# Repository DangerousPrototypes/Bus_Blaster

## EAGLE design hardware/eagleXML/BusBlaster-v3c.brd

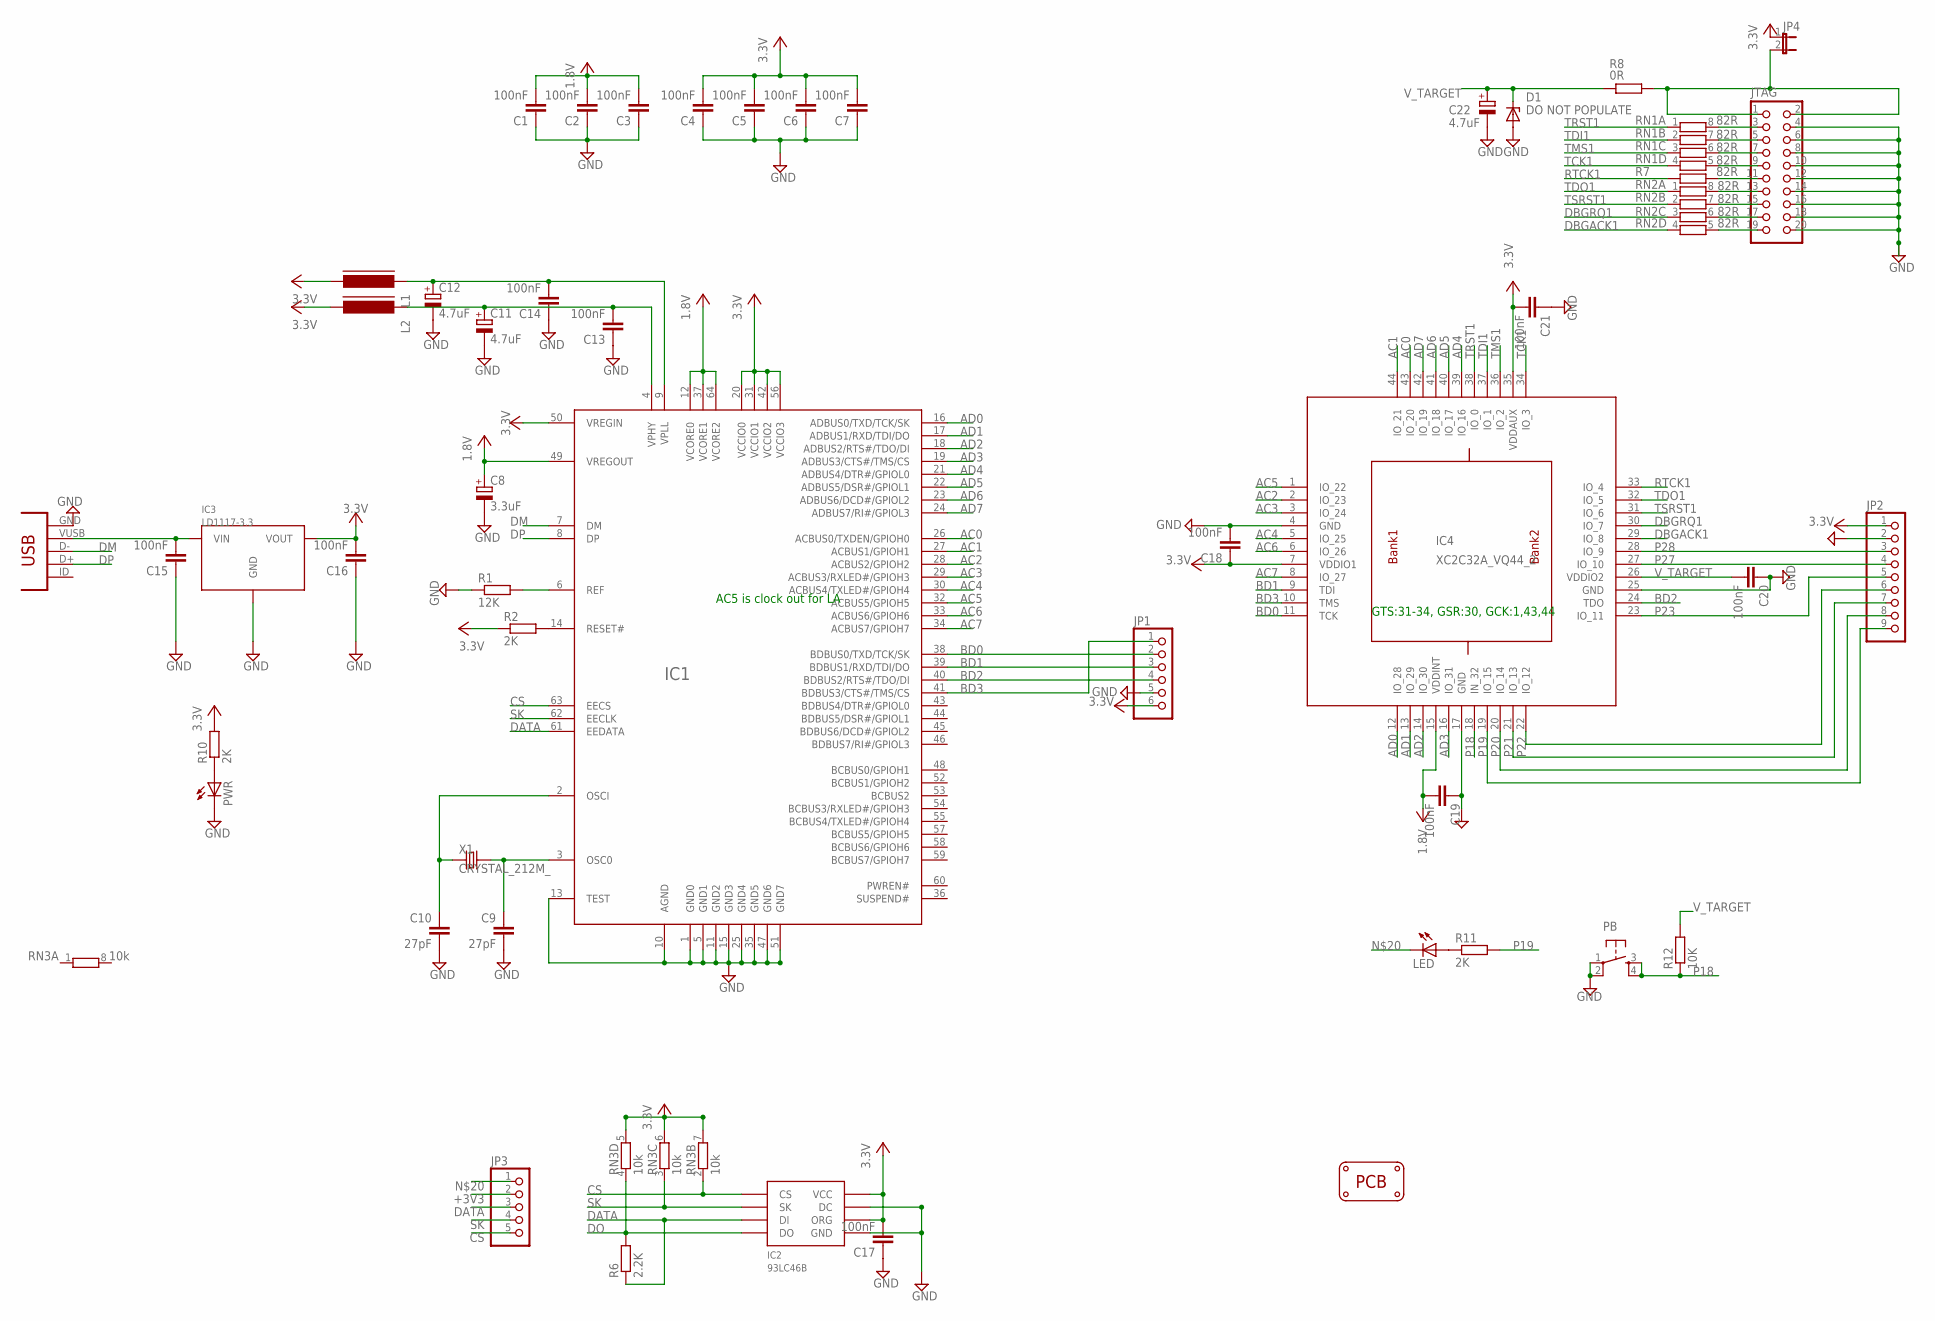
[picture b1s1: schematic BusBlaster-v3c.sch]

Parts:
C1, C2, C3, C4, C5, C6, C7, C13, C14, C15, C16, C17, C18, C19, C20, C21: 100nF; C603
C8: 3.3uF; SMC_A
C9, C10: 27pF; C603
C11, C12, C22: 4.7uF; SMC_A
D1: DO NOT POPULATE; SOD-123
IC1: FT2232H; LQFP64
IC2: 93LC46B; SOIC8
IC3: LD1117-3.3; SOT223
IC4: XC2C32A_VQ44_2; VQ44
JP1: PINHD-1X6; 1X06
JP2: PINHD-1X9; 1X09
JP3: PINHD-1X5; 1X05
JP4: JP1EJP; 1X02
JTAG: CON_HEADER_2X10-SHROUDED; PINSHRD_PTH_2X10
L1, L2: FERRITE_BEAD603; FB603
LED: LED805; LED-805
PB: SW-SMD-SMALL; TACT_SWITCH_SMALL
PCB3: PCB_DP_RECTANGLE-80X49; DP8049_V1
PWR: LEDCHIPLED_0805; CHIPLED_0805
R1: 12K; R603
R2, R10, R11: 2K; R603
R6: 2.2K; R603
R7: 82R; R603
R8: 0R; R1206
R12: 10K; R603
RN1, RN2: 82R; RN8P-4R-CRA06S
RN3: 10k; RN8P-4R-CRA06S
USB: CON-USB-MINI-BUSB1; CONN_USB_MINI-B
X1: CRYSTAL_212M_; 4X6

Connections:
1.8V: C1.2, C2.2, C3.2, C8.+, C19.2, IC1.12 (VCORE0), IC1.37 (VCORE1), IC1.49 (VREGOUT), IC1.64 (VCORE2), IC4.15 (VDDINT)
+3V3: C4.2, C5.2, C6.2, C7.2, C16.2, C17.2, C18.1, C21.2, IC1.20 (VCCIO0), IC1.31 (VCCIO1), IC1.42 (VCCIO2), IC1.50 (VREGIN), IC1.56 (VCCIO3), IC2.6 (ORG), IC2.8 (VCC), IC3.2 (VOUT), IC4.7 (VDDIO1), IC4.35 (VDDAUX), JP1.6, JP2.1, JP3.2, JP4.1, L1.2, L2.2, R2.1, R10.2, RN3.5 (2), RN3.6 (2), RN3.7 (2)
AC0: IC1.26 (ACBUS0/TXDEN/GPIOH0), IC4.43 (IO_20)
AC1: IC1.27 (ACBUS1/GPIOH1), IC4.44 (IO_21)
AC2: IC1.28 (ACBUS2/GPIOH2), IC4.2 (IO_23)
AC3: IC1.29 (ACBUS3/RXLED#/GPIOH3), IC4.3 (IO_24)
AC4: IC1.30 (ACBUS4/TXLED#/GPIOH4), IC4.5 (IO_25)
AC5: IC1.32 (ACBUS5/GPIOH5), IC4.1 (IO_22)
AC6: IC1.33 (ACBUS6/GPIOH6), IC4.6 (IO_26)
AC7: IC1.34 (ACBUS7/GPIOH7), IC4.8 (IO_27)
AD0: IC1.16 (ADBUS0/TXD/TCK/SK), IC4.12 (IO_28)
AD1: IC1.17 (ADBUS1/RXD/TDI/DO), IC4.13 (IO_29)
AD2: IC1.18 (ADBUS2/RTS#/TDO/DI), IC4.14 (IO_30)
AD3: IC1.19 (ADBUS3/CTS#/TMS/CS), IC4.16 (IO_31)
AD4: IC1.21 (ADBUS4/DTR#/GPIOL0), IC4.39 (IO_16)
AD5: IC1.22 (ADBUS5/DSR#/GPIOL1), IC4.40 (IO_17)
AD6: IC1.23 (ADBUS6/DCD#/GPIOL2), IC4.41 (IO_18)
AD7: IC1.24 (ADBUS7/RI#/GPIOL3), IC4.42 (IO_19)
BD0: IC1.38 (BDBUS0/TXD/TCK/SK), IC4.11 (TCK), JP1.2
BD1: IC1.39 (BDBUS1/RXD/TDI/DO), IC4.9 (TDI), JP1.3
BD2: IC1.40 (BDBUS2/RTS#/TDO/DI), IC4.24 (TDO), JP1.4
BD3: IC1.41 (BDBUS3/CTS#/TMS/CS), IC4.10 (TMS), JP1.1
CS: IC1.63 (EECS), IC2.1 (CS), JP3.5, RN3.2 (1)
DATA: IC1.61 (EEDATA), IC2.3 (DI), JP3.3, R6.1
DBGACK1: IC4.29 (IO_8), RN2.4 (1)
DBGRQ1: IC4.30 (IO_7), RN2.3 (1)
DM: IC1.7 (DM), USB.D-
DO: IC2.4 (DO), R6.2, RN3.4 (1)
DP: IC1.8 (DP), USB.D+
unnamed: C9.1, IC1.3 (OSC0), X1.2 (X2)
unnamed: C10.1, IC1.2 (OSCI), X1.1 (X1)
unnamed: IC1.14 (RESET#), R2.2
unnamed: IC1.6 (REF), R1.2
unnamed: C15.2, IC3.3 (VIN), USB.VUSB
unnamed: PWR.A, R10.1
unnamed: JTAG.3, RN1.8 (2)
unnamed: LED.A, R11.1
unnamed: JTAG.5, RN1.7 (2)
unnamed: JTAG.7, RN1.6 (2)
unnamed: JTAG.9, RN1.5 (2)
unnamed: JTAG.11, R7.2
unnamed: JTAG.13, RN2.8 (2)
unnamed: JTAG.15, RN2.7 (2)
unnamed: JTAG.17, RN2.6 (2)
unnamed: JTAG.19, RN2.5 (2)
unnamed: C1.1, C2.1, C3.1, C4.1, C5.1, C6.1, C7.1, C8.-, C9.2, C10.2, C11.-, C12.-, C13.1, C14.1, C15.1, C16.1, C17.1, C18.2, C19.1, C20.1, C21.1, C22.-, D1.A, IC1.1 (GND0), IC1.5 (GND1), IC1.10 (AGND), IC1.11 (GND2), IC1.13 (TEST), IC1.15 (GND3), IC1.25 (GND4), IC1.35 (GND5), IC1.47 (GND6), IC1.51 (GND7), IC2.5 (GND), IC2.7 (DC), IC3.1 (GND), IC4.4 (GND), IC4.17 (GND), IC4.25 (GND), JP1.5, JP2.2, JP3.1, JTAG.4, JTAG.6, JTAG.8, JTAG.10, JTAG.12, JTAG.14, JTAG.16, JTAG.18, JTAG.20, LED.C, PB.1, PB.2, PWR.C, R1.1, USB.GND
P18: IC4.18 (IN_32), PB.3, PB.4, R12.1
P19: IC4.19 (IO_15), JP2.9, R11.2
P20: IC4.20 (IO_14), JP2.8
P21: IC4.21 (IO_13), JP2.7
P22: IC4.22 (IO_12), JP2.6
P23: IC4.23 (IO_11), JP2.5
P27: IC4.27 (IO_10), JP2.4
P28: IC4.28 (IO_9), JP2.3
RTCK1: IC4.33 (IO_4), R7.1
SK: IC1.62 (EECLK), IC2.2 (SK), JP3.4, RN3.3 (1)
TCK1: IC4.34 (IO_3), RN1.4 (1)
TDI1: IC4.37 (IO_1), RN1.2 (1)
TDO1: IC4.32 (IO_5), RN2.1
TMS1: IC4.36 (IO_2), RN1.3 (1)
TRST1: IC4.38 (IO_0), RN1.1
TSRST1: IC4.31 (IO_6), RN2.2 (1)
VPHY: C11.+, C13.2, IC1.4 (VPHY), L2.1
VPLL: C12.+, C14.2, IC1.9 (VPLL), L1.1
V_TARGET: C20.2, C22.+, D1.C, IC4.26 (VDDIO2), R8.1, R12.2
V_TARGET_UNREG: JP4.2, JTAG.1, JTAG.2, R8.2

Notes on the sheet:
GTS:31-34, GSR:30, GCK:1,43,44
AC5 is clock out for LA

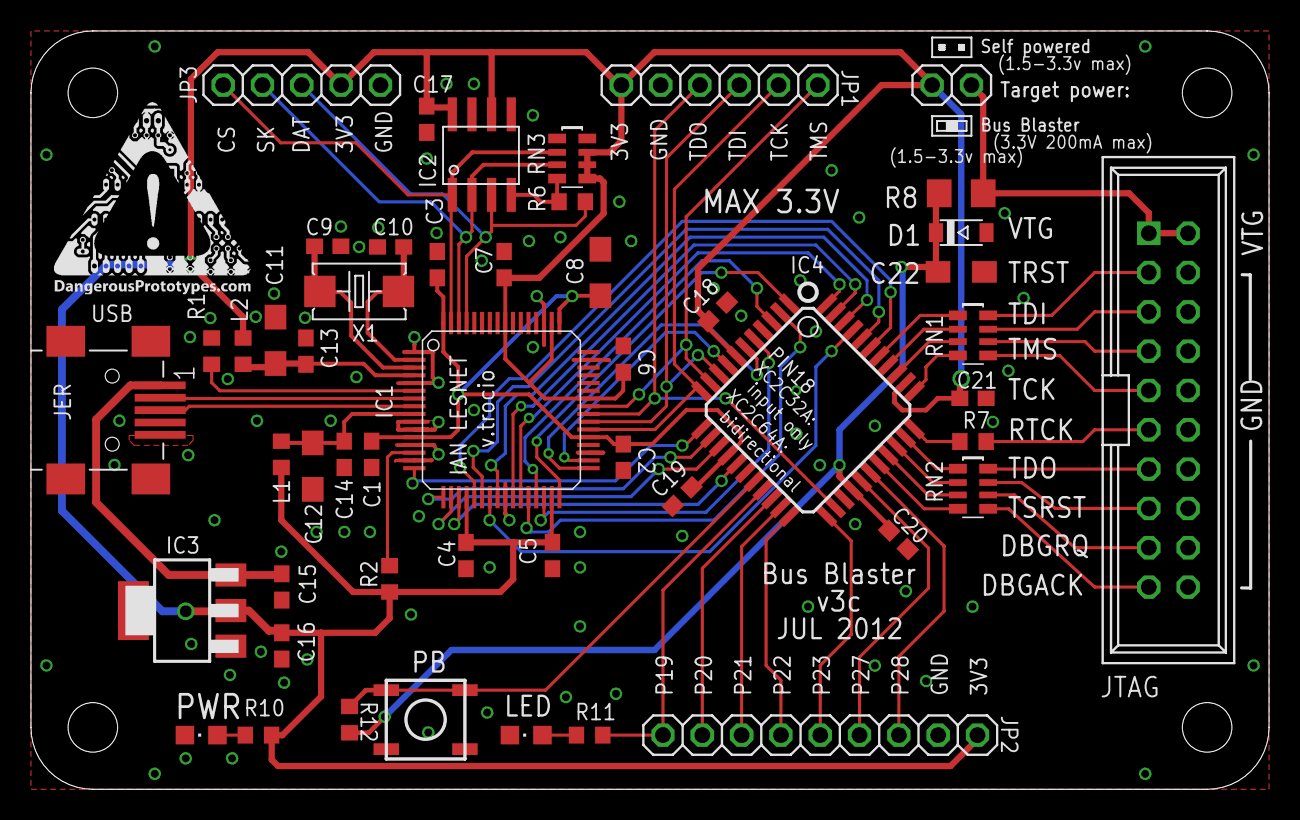
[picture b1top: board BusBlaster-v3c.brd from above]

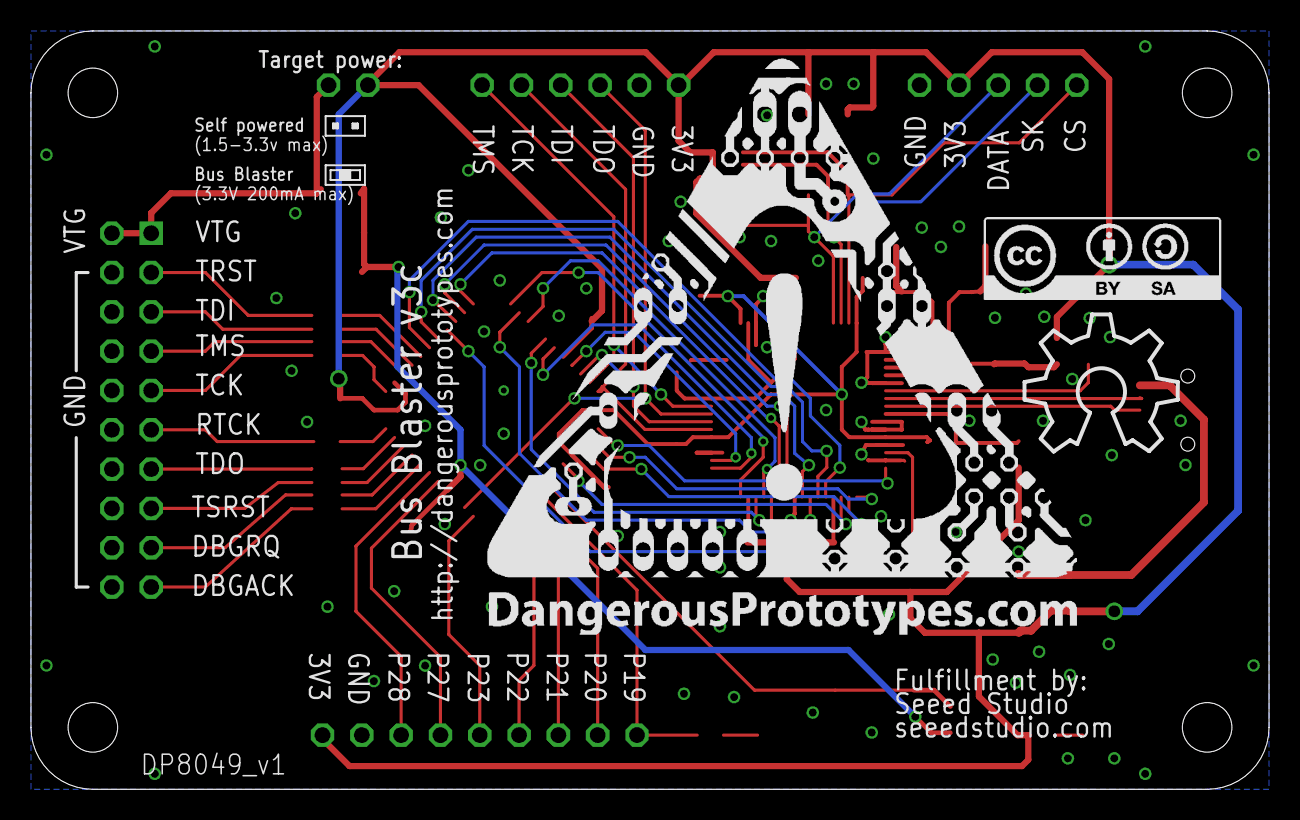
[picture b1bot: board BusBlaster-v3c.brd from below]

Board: 2 copper layers, 80.0 x 49.0 mm, 59 parts (5 on the bottom side), 66 nets.

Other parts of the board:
U$1: DP_LOGO_ART_1.5X1.5
U$2: DP_LOGO_ART_0.5X0.5
U$3: CC-BY-SA
U$5: OSHW_10X350_NOTEXT
U$6, U$9: adasdsd; JUMP2_DESC_ON
U$7, U$8: JUMP2_DESC_OFF

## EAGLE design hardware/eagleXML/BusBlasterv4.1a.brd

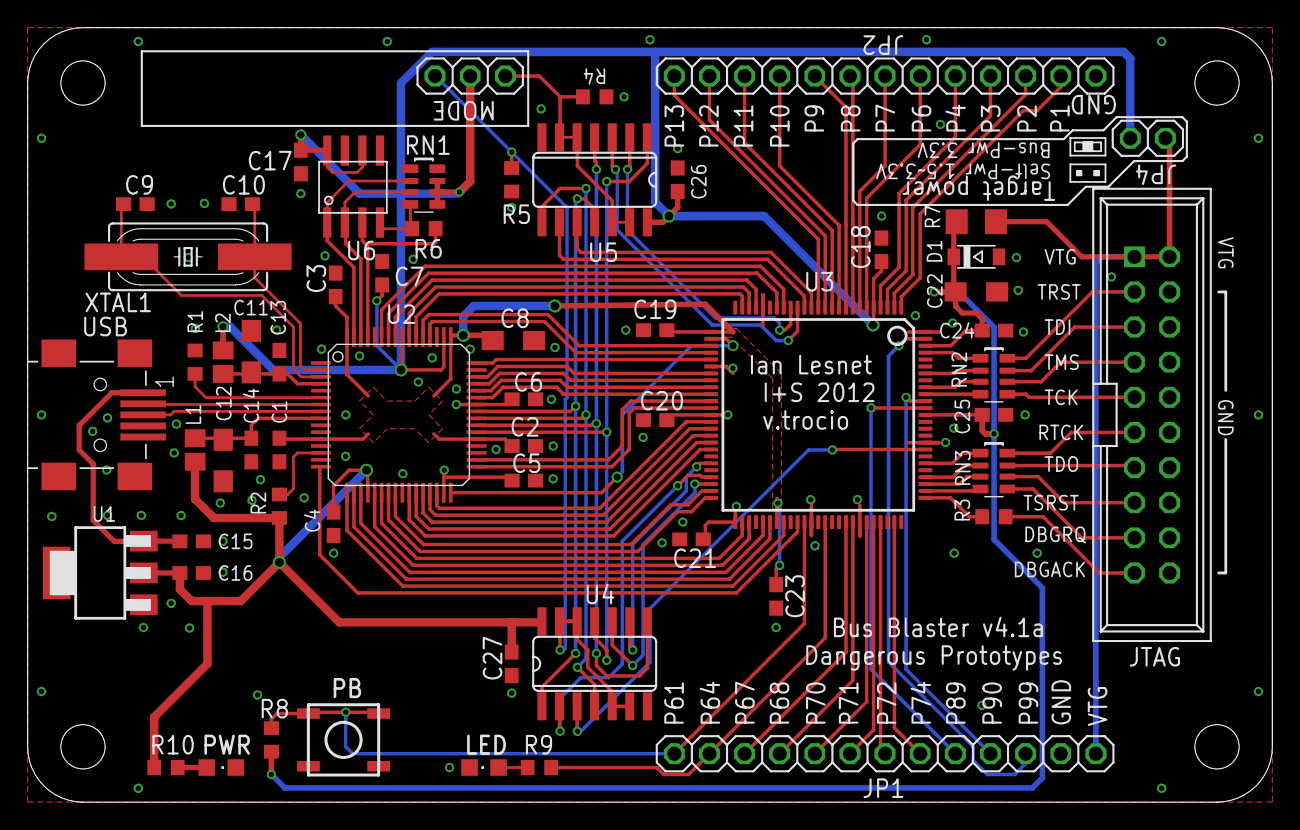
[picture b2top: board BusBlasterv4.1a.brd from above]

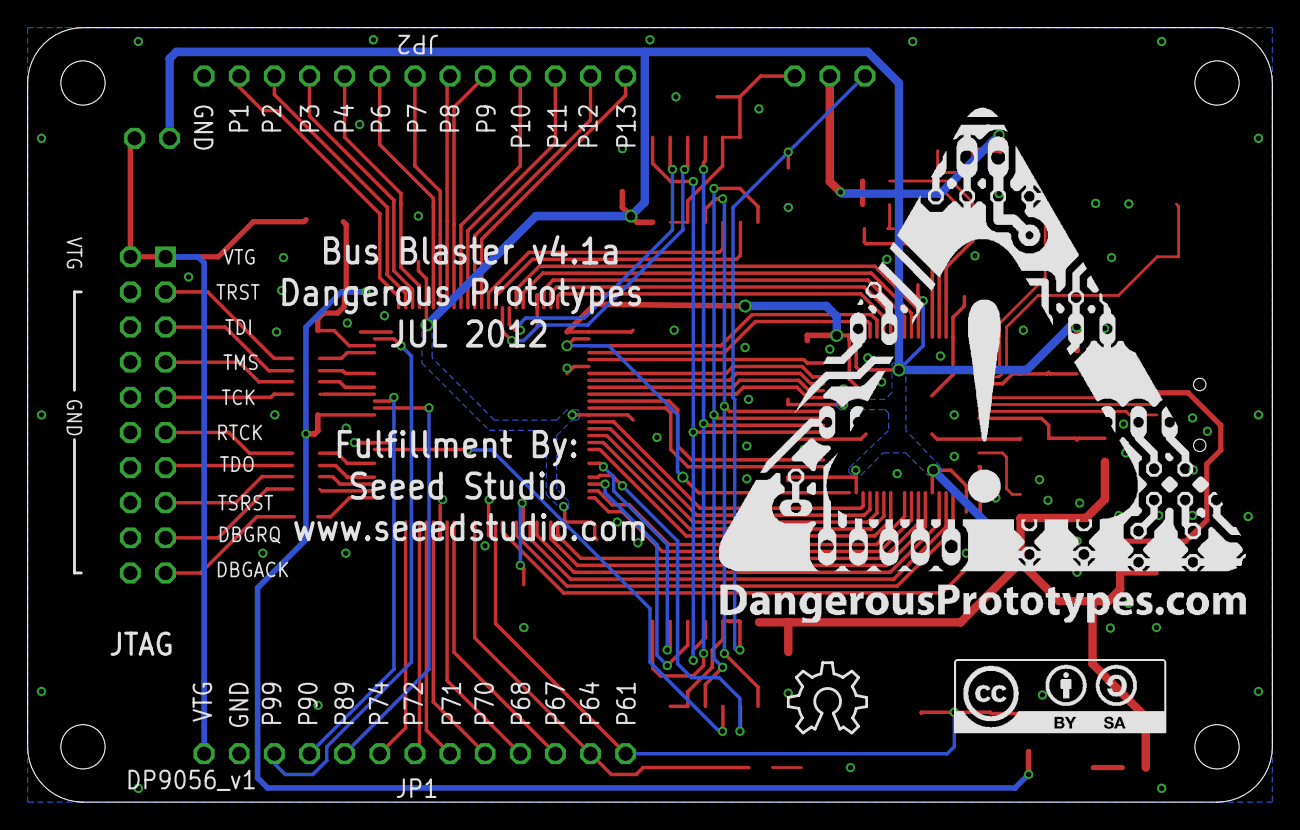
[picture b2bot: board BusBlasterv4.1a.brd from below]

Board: 2 copper layers, 90.0 x 56.0 mm, 65 parts (3 on the bottom side), 103 nets.

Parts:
C1, C2, C3, C4, C5, C6, C7, C13, C14, C15, C16, C17, C18, C19, C20, C21, C23, C24, C25, C26, C27: 100nF; C603
C8: 3.3uF; SMC_A
C9, C10: 27pF; C603
C11, C12, C22: 4.7uF; SMC_A
D1: DO NOT POPULATE; SOD-123
JP1, JP2: 1X13
JP4: 1X02
JTAG: CON_HEADER_2X10-SHROUDED; PINSHRD_PTH_2X10
L1, L2: FB603
LED: LED-805
MODE: 1X03
PB: TACT_SWITCH_SMALL
PCB1: PCB_DP_RECTANGLE-56X90; DP9056_V1
PWR: CHIPLED_0805
R1: 12K; R603
R2, R9: 1K; R603
R3: 82R; R603
R4, R5, R8: 10K; R603
R6: 2.2K; R603
R7: 0R; R1206
R10: 470; R603
RN1: 10k; RN8P-4R-CRA06S
RN2, RN3: 82R; RN8P-4R-CRA06S
U1: SOT223
U2: LQFP64@1
U3: XC2C64A; VQ100
U4, U5: 4066D; SO14
U6: 93LC46B; SOIC8
U$1: DP_LOGO1.5X1.5; DP_LOGO_ART_1.5X1.5
U$2: CC-BY-SA
U$3: OSHW_8X200_NOTEXT
U$4: LABEL_JUMPER_1X3; JUMP3_DESC
U$7: LABEL_JUMPER_1X2; JUMP2_DESC
USB: CON-USB-MINI-BUSB1; CONN_USB_MINI-B
XTAL1: HC-49U

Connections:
1: JP2.2, U3.1
1.8V: C1.2, C2.2, C3.2, C8.+, C19.2, C23.2, U2.12, U2.37, U2.49, U2.64, U3.26, U3.57
2: JP2.3, U3.2
3: JP2.4, U3.3
4: JP2.5, U3.4
6: JP2.6, U3.6
7: JP2.7, U3.7
8: JP2.8, U3.8
9: JP2.9, U3.9
10: JP2.10, U3.10
11: JP2.11, U3.11
12: JP2.12, U3.12
13: JP2.13, U3.13
61: JP1.13, PB.3, PB.4, R8.1, U3.61
64: JP1.12, R9.2, U3.64
67: JP1.11, U3.67
68: JP1.10, U3.68
70: JP1.9, U3.70
71: JP1.8, U3.71
72: JP1.7, U3.72
74: JP1.6, U3.74
89: JP1.5, U3.89
90: JP1.4, U3.90
99: JP1.3, U3.99
+3V3: C4.2, C5.2, C6.2, C7.2, C16.2, C17.2, C18.2, C20.2, C21.2, C26.2, C27.2, JP4.1, L1.2, L2.2, MODE.2, R2.1, R10.2, RN1.5, RN1.6, RN1.7, U1.2, U2.20, U2.31, U2.42, U2.50, U2.56, U3.5, U3.38, U3.51, U4.14, U5.14, U6.6, U6.8
AC0: U2.26, U3.43
AC1: U2.27, U3.42
AC2: U2.28, U3.41
AC3: U2.29, U3.40
AC4: U2.30, U3.39
AC5: U2.32, U3.27
AC6: U2.33, U3.37
AC7: U2.34, U3.36
AD0: U2.16, U3.60
AD1: U2.17, U3.58
AD2: U2.18, U3.56
AD3: U2.19, U3.55
AD4: U2.21, U3.53
AD5: U2.22, U3.52
AD6: U2.23, U3.50
AD7: U2.24, U3.49
BC0: U2.48, U3.30
BC1: U2.52, U3.29
BC2: U2.53, U3.28
BC3: U2.54, U3.24
BC4: U2.55, U3.23
BC5: U2.57, U3.22
BC6: U2.58, U3.19
BC7: U2.59, U3.18
BD0: U2.38, U4.11, U5.1
BD0_: U3.17, U5.2
BD1: U2.39, U4.8, U5.4
BD1_: U3.16, U5.3
BD2: U2.40, U4.4, U5.8
BD2_: U3.15, U5.9
BD3: U2.41, U4.1, U5.11
BD3_: U3.14, U5.10
BD4: U2.43, U3.35
BD5: U2.44, U3.34
BD6: U2.45, U3.33
BD7: U2.46, U3.32
CS: RN1.2, U2.63, U6.1
DATA: R6.1, U2.61, U6.3
DBGACK1: R3.1, U3.76
DBGRQ1: RN3.4, U3.77
DM: U2.7, USB.D-
DO: R6.2, RN1.4, U6.4
DP: U2.8, USB.D+
GND: C1.1, C2.1, C3.1, C4.1, C5.1, C6.1, C7.1, C8.-, C9.2, C10.2, C11.-, C12.-, C13.1, C14.1, C15.1, C16.1, C17.1, C18.1, C19.1, C20.1, C21.1, C22.-, C23.1, C24.1, C25.2, C26.1, C27.1, D1.A, JP1.2, JP2.1, JTAG.4, JTAG.6, JTAG.8, JTAG.10, JTAG.12, JTAG.14, JTAG.16, JTAG.18, JTAG.20, LED.C, PB.1, PB.2, PWR.C, R1.1, R4.1, R5.2, U1.1, U2.1, U2.5, U2.10, U2.11, U2.13, U2.15, U2.25, U2.35, U2.47, U2.51, U3.21, U3.31, U3.62, U3.69, U3.84, U3.100, U4.7, U5.7, U6.5, U6.7, USB.GND
unnamed: C9.1, U2.3, XTAL1.2
unnamed: C10.1, U2.2, XTAL1.1
unnamed: R2.2, U2.14
unnamed: R1.2, U2.6
unnamed: C15.2, U1.3, USB.VUSB
unnamed: PWR.A, R10.1
unnamed: LED.A, R9.1
unnamed: JTAG.3, RN2.8
unnamed: JTAG.5, RN2.7
unnamed: JTAG.7, RN2.6
unnamed: JTAG.9, RN2.5
unnamed: JTAG.11, RN3.8
unnamed: JTAG.13, RN3.7
unnamed: JTAG.15, RN3.6
unnamed: JTAG.17, RN3.5
unnamed: JTAG.19, R3.2
unnamed: MODE.3, R5.1, U4.5, U4.6, U4.12, U4.13
unnamed: MODE.1, R4.2, U5.5, U5.6, U5.12, U5.13
RTCK1: RN3.1, U3.81
SK: RN1.3, U2.62, U6.2
TCK: U3.48, U4.10
TCK1: RN2.4, U3.91
TDI: U3.45, U4.9
TDI1: RN2.2, U3.94
TDO: U3.83, U4.3
TDO1: RN3.2, U3.79
TMS: U3.47, U4.2
TMS1: RN2.3, U3.92
TRST1: RN2.1, U3.97
TSRST1: RN3.3, U3.78
VPHY: C11.+, C13.2, L2.1, U2.4
VPLL: C12.+, C14.2, L1.1, U2.9
VT: C22.+, C24.2, C25.1, D1.C, R7.1, R8.2, U3.88, U3.98
VTG: JP1.1, JP4.2, JTAG.1, JTAG.2, R7.2

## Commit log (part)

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2012-07-23 updated v3 and v4 shrouded header with the correct silk, fix v4 "Fufillment" mispelling. Please use latest v3c and v4.1a
2012-07-23 Bus Blaster v3c 3d model and rendering
2012-07-24 Added parts: KSZ8851SNL, TPS6120X, 2X08 HEADER, 3x6 mm 2pins switch, 1.8" TFT LCD Added 2x10 Shrouded Pin Header variant to existing 2x10 Header
2012-07-25 Bus Blaster v3 svg files, and BoM
2012-07-25 Exploaded sob case assemplby 3d model
2012-08-03 Parts Added: 3.3v, 5v, vusb, gnd supply symbols, 2 and 3 pins wire to board screw terminal block, USB AF SMD. Parts updated: 2 and 3 pins jumper description change layer to tDocu.
2012-08-08 Added 74AC573 in SOIC-20 changed Oscillator prefix to 'X'
2012-08-09 Added: FT311D in LQFP-32
2012-08-14 Changes to USB interrupt from JTR
2012-08-14 small fix to BPv4 bootloader (comment in wrong place)
    http://dangerousprototypes.com/forum/viewtopic.php?f=28&t=3441&start=45#p42466
2012-08-14 UART inverse transmit pin was omitted in all BP versions:
    http://dangerousprototypes.com/track/view.php?id=47
2012-08-16 Bus Pirate Demo board firmware
2012-08-20 Added device: 23LC1024 SRAM in SOIC-8
2012-08-27 update to blog theme with header fix, switch for contest theme.
2012-08-27 blog theme contest template update
2012-09-04 Added devices: 74HC595 and 74141 Added footprint: DIL16 Updated: removed extra mounting holes on DP6060 Added schematic symbol: 12V, -12V and -5V Added Logo: Flame logo
2012-09-04 revised credit card sized PCB based on ISO.IEC 7810 ID-1 identification cards sizes, size changed from 85 x 56 mm to 85.60 x 53.98 mm
2012-09-04 update Standard rectangular PCBs devices
2012-09-06 little file reshuffeling in the ATX laser cutt files
2012-09-06 1.8 TFT design files
2012-09-07 Added: IN-12 Nixie tube display, IN-12 Socket cutout footprint Fixed: IN-12 Socket
2012-09-10 Sick of beige generic model, and render images
2012-09-12 first commit of DP KiCAD part library
2012-09-12 DP KiCAD parts
2012-09-13 .lib and .mod files converted using eagle2kicad-0.d.ulp from http://www.modulbot.com/download.html Fixed undefined DRAW command when loading to symbol library to KiCAD
2012-09-19 Added: INA138 device
2012-09-20 Bus Pirate v4 Sick of Beige case laser cutting files and partlist(BOM)
2012-09-24 maker faire new york banner
2012-09-24 Done the changes related to global->instance variables suggested by Jim, corrected some variable name typos and got rid of console debug messages.
2012-09-24 Added new Logic shrimp v2b, this version uses 23LC1024 SRAM
2012-09-25 initial Smoke Tester project folder
2012-09-25 Board files
2012-09-26 swapped drain and source pin of the p-mosfet controlling fuse blown switch
2012-09-27 OHS 2012 presentations
2012-10-01 Smoke Tester 3D model and renders
2012-10-07 Adding a vertical ATX socket from the Molex MiniFit Jr. line.
    Discrete sockets (key'ed and rectangular) are provided in separate files so they can be easily added to create different configurations. Each socket is made to be "stackable" on both sides, so you'll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
2012-10-07 adding an assortment of 3d models. They should all have origins centered properly about the pins. These were not checked thoroughly, but do appear to be generally correct. Most models are tweaked fro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
    The QFN32 is original and should be extremely easy to scale and accommodate other numbers of pins.
2012-10-08 Added: D8035E VFD board, composed of 3 boards. Board A, B and C
2012-10-08 Added: PTH variant of 2.1mm DC Barrel Connector with milled hole pads
2012-10-08 VFD Board, render and 3D model..
2012-10-10 first cut at molex KK series connectors. The 1x2 should be modeled in such a way that it's side stackable, so it will be easy to make additional even numbered connectors. These were based on a model 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
    These should be "close enough" for most purposes, alignment appears to be off a bit on the 4pos header though.
2012-10-10 ATO fuse clip, ATO fuse holder, and ATO jumper. Created from a minimal datasheet from Littlefuse 01000057Z.
    Can be found at Mouser:
    http://www.mouser.com/ProductDetail/Littelfuse/01000057Z/?qs=sGAEpiMZZMtN62bhLohzxVzkiLrmT5C%2f
    Other alternatives for high current voltage selection were discussed here:
    http://dangerousprototypes.com/forum/viewtopic.php?f=56&t=4509
2012-10-10 Added: 3D models for 2 trough-hole IC and a metalized Capacitor.
2012-10-10 Added SF303GJ26-3 JOYSTICK
2012-10-16 rearanged SID SVN, and aded the mauf resources and sales page foleder...as wlell as the sales page txt
2012-10-18 adding some 3.5mm side stacking screw terminals. The model is based on a phoenix 1984617, but should be representative of most side-stacking 3.5mm screw terminals.
    An individual component is also included, which should makes it really easy to quickly generate any number of positions (just do a move/copy, explode the components, and erase the lines along the sea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
2012-10-18 correcting the naming for the 2512 resistor model
2012-10-18 Added device: MicrosSD fold type socket, PIC24F16KA102, 1x2 SMD solder jumper. fix Arduino 1x8 header containing pin 8 - 13, offset ed location.
2012-10-18 Bus Blaster v4 test buffer project
2012-10-19 fix PIC24F16KA102 vector text overlap on its symbol Add SOIC-14 package on PIC16F1823
2012-10-22 Soldering Iron Driver renderings and 3D model
2012-10-25 Added projects: DP6037 protoboard v1, DP6037_PTH v1 and DP6037_SMD v1
2012-10-25 add project: FT230x_LTC4053_BB_proto_area.v1a
2012-10-25 Add project: FT311 breakout board v1b
2012-10-30 added: 1x08 and 1x06 0.1 pitch SMD female header
2012-10-30 added DIL-28 PTH to SMD socket
2012-10-31 Added manufacturing files for updated ATX board acrylic case
2012-11-05 added: 4.5 x 4.5 SMD Trimmer, model 3314G
2012-11-07 added right angled 0.1inch 1x06 male header. expanded M1X4, M1X6, M1X8 pads to 1.632mm and drill size to 1.02mm
2012-11-13 added a 1x06 right angled header and a 2x03 SMD straight male headers.
2012-11-15 initial xQFP protoboards folder
2012-11-15 add 0.50mm, 0.65mm and 0.80mm xQFP V1 protoboards
2012-11-22 added ICSP with pogo pin as connector
2012-11-22 added v2.1, LCD_Backpack_1.8_TFT with pogo footprint ICSP
2012-11-30 added 0.50, 0.65 and 0.80 mm pitch universal QFP footprint and QFP breakout board These footprint are licensed: CC-BY-SA
2012-12-05 commit PIC TQFP-100 breakout v1 and v2
2012-12-06 added protoboard with 0.65mm and 0.80mm xQFP
2012-12-07 added BP v4e, fix odd angled placement, no 45 degrees placement anymore. replaced ICSP header with miniature ICSP footprint
2012-12-07 updated 0.5, 0.65 and 0.8 xQFP protoboards by adding a USB footprint. 2-3 SOT-23-6 footprints were removed to fit the usb
2012-12-10 added a 6 way SOLO stacker connector and footprint
2012-12-12 added dual xQFP pitch protoboards, pitch combined are 0.50 + 0.65 mm, 0.80 + 0.50 mm and 0.80 + 0.65 mm. these boards were also having a micro usb footprint under its mini-b footprint
2012-12-12 added TSSOP-20 variant of TXB0108, voltage level translator
2012-12-14 fix pad, changed via to a pad. new board named v1b
2012-12-20 added: 1x1 PTH hole for protoboard filler changed "board name" of DP standard PCB name(on the bottom) to ">NAME" so it will now be smashable a can be moved around.
2012-12-20 made DP PCB label name to an attribute type, the label can now be smash and moved.
2013-01-07 added 0603 SMD LED, 1x02 and 1x03 right angled 0.1 inch pitched PTH header
2013-01-09 Patches applied for Bus Pirate Tracker isues 66 and 73 http://dangerousprototypes.com/track/view.php?id=66 http://dangerousprototypes.com/track/view.php?id=73
    66: bpWlongdecf() fails to correctly print out some values
    73: Improving Frequency Measurement Resolution & Gremlins
    patch 66 baseIO.c bpWlongdecf() function tested, and working.
    Patch 73 untested, but compiles and doesn't break any of the functions.
2013-01-10 Bus Pirate - AUXpin.c. Cleaned the code a bit, deleted a huge commented out section, and applyed the patch in issue #65 http://dangerousprototypes.com/track/view.php?id=65
2013-01-11 Bus Pirate firmware -v4 pull up voltage control add to bin protocol. as per issue 63 http://dangerousprototypes.com/track/view.php?id=63 patch available at the link above, and is applied to rev2082
2013-01-14 A slight change in variable definition in procMenu.c, and indent fix in I2C.c
2013-01-16 Bus Pirate firmware issue 51 minor fix to the protos function pointer array, in the BP_USE_I2C section. nulfunc changed to I2Cstop.. http://dangerousprototypes.com/track/view.php?id=51
2013-01-18 HEx files ready for upload through bootloader for BP v3 and v4 6.3r2088
2013-01-22 Bus Pirate firmware - issue 50 added support for RAW mode as well, entered through 'w'
    so now it;s rd foe decimal, rx for HEX, rb for BIN and rw for raw
2013-01-25 Added PTH 2x7 0.1" header, fix TSSOP-20 footprint pad arrangement, fix 74AC573 TSSOP-20 pin numbering
2013-01-25 Test
2013-01-25 * Initial check-in.
2013-01-25 * Added bootloadable firmware.
2013-01-25 * Added Gerber files.
2013-01-27 * Added color scheme for logic shrimp probe cables.
2013-01-28 Bus Pirate Firmware - issue 53. Basic scripting engine put back into v6.2.... http://dangerousprototypes.com/track/view.php?id=53
2013-01-31 Bus Pirate Firmware issue #89 - adding UART communications in debugging mode, to activate, #define BPV4_DEBUG, to deactivate comment it out in base.h.. This lets you to connect your debugger and run 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
2013-02-01 update v3c and v4.1a, change value of R8 to 0R and RN1 and RN2 to 82R, unpopulate D1 on BB v3c, change value of R7 to 0R and unpopulate D1 on BB v4.1a. added final v3c and v4.1a to package folder
2013-02-01 * Improved META command.
2013-02-14 * Increased the offset for the ICSP holes from 2 to 4 mils.
2013-02-18 add: PTH ferrite bead 10mm pitch, 20x20mm 8x8 LED matrix
2013-02-19 Mark pin 1 of DIP8, DIP14, DIP14W as this is automatically changed to a square pad by DRC check. Corrected SO-8's name and values labels to their proper layers
2013-02-19 Bus Blaster v4 manufacturing test package
2013-02-19 update parts list of v3c and v4.1a, copied updated parts list to /hardware folder, made manufacturing resources files for v4.1.
2013-02-28 * Renamed folder.
2013-03-07 updates on v3.8 USB connector now in micro-B All SMD LEDs are in LED603 IO shrouded header fix, notch is facing outward not much change on the USB D+ D- line just did route them to have almost the sa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
2013-03-07 IO pinout re-arrange to be like bpv4
2013-03-11 Added single pad with 40mil and 32 mil drill size both square and round Added SOIC 14W, 18W, 8NW, 14NW and 16NW footprints N-narrow, W-wide, NW - Narrow + Wide Added 10cm x 10cm (DP100100) in SoB
2013-03-13 change U3 of parts list from a 44 pin to 100 pin XC2C64A-7VQG100C CPLD
2013-03-14 I know the SPI module works with the changes made to the underlying communication tools. However, all the other modules need some verification. I'll probably try to put together some unit-tests. Howe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
2013-03-15 added 24AA04 DIP, 25AA04, MCP3001, MCP4901, MCP9701, TC74 TO220-5 fix some text on POT symbol
2013-03-15 * Final fixes.
2013-04-03 Added: MCP4131 Digital Potentiometer Tester Probe socket QFN 12 and 16 pins 3x3cm QFN 16, 20 and 24 4x4 cm SOIC Narrow+Wide 18, 20, 24 and 28 pins
2013-04-16 Initial Folder for Test Probe Adapter
2013-04-23 added gerbmerge config creator ULP
2013-04-25 Fixed the sizing issue mentioned in http://dangerousprototypes.com/forum/viewtopic.php?f=63&t=4563&start=15#p51915
2013-05-08 moved anchor/reference point of SoB PCBs to its center
2013-06-23 * Fixed https://github.com/jawi/ols/issues/179
2013-06-23 * Updated version info.
2013-07-09 Bus Pirate - applied patch for AVR DUDE, tracker 113 http://dangerousprototypes.com/track/view.php?id=113 compiled to version bp6.3r2151, added hex files
2013-07-23 Added: MCP7940 I2C RTC with SRAM in SOIC8 and DIP8, Alternate 3 Pins Voltage Regulator to accomodate 4th pin as tab connection. Revised VREG 3 PINS now with TO-220 Horizontal footprint
2013-09-28 Update to use proper timeouts.
2013-09-28 merging PyBusPirateLite branch back into mainline
2014-01-10 changed SMD SMC-A pad size from 1.60 x 1.40 to 1.40 x 1.80 changed SMD SMC-B pad size from 1.60 x 2.40 to 1.40 x 2.80 added new SMD SMC-C footprint added part MBI5026 (SOIC-24 variant) 16-Bit constan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
2014-02-03 Initial hardware files uploaded
2014-02-11 SMD Tape cutting controller intended to automatically dispense SMD parts
2014-02-11 An SMD Tape cutting controller intended to automatically dispense SMD parts
2014-02-11 uploaded directories and files
2014-02-23 SPI mode } command was giving errors, busPirateCore.c line 225 now maps to SPIstop for stopR. Should fix it. Untested.
2014-03-21 correct EEPROM for v2/2.5, v3c and v4a, old EEPROM value was non 3.3V compliant (93C46), replaced with 93LC46B. updated schematic, wiki, BOM/Partlist. Board and gerbers still the same
